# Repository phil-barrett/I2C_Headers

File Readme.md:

Welcome to I2C_Headers.  This repository is for HW designs that use the I2C header interface present on Brookwood Designs grblHAL Breakout Boards.

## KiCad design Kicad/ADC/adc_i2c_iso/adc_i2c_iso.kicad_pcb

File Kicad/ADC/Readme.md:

A simple Isolated I2C ADC interface.

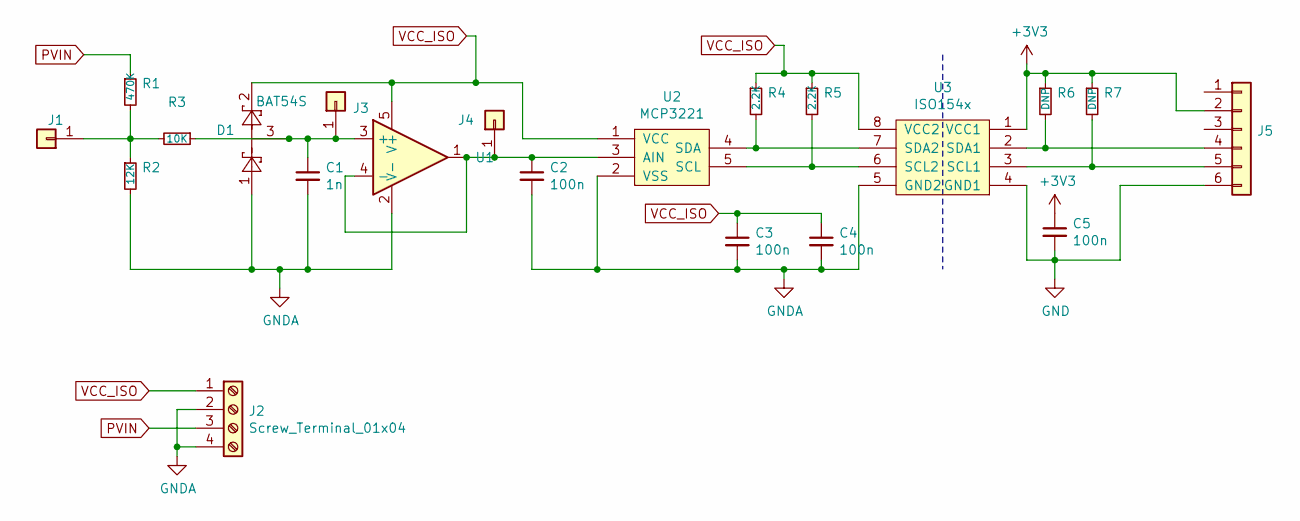
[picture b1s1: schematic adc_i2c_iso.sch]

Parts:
C1: 1n; C_0805
C2, C3, C4, C5: 100n; C_0805
D1: BAT54S; SOT-23
J1, J3, J4: Conn_01x01; Pin_Header_Straight_1x01_Pitch2.00mm
J2: Screw_Terminal_01x04; plug_term_p4
J5: Conn_01x06; Pin_Header_Straight_1x06_Pitch2.54mm
R1: 470K; R_1206
R2: 12K; R_1206
R3: 10K; R_0805; LCSC C17414
R4, R5: 2.2K; R_0805; LCSC C17520
R6, R7: DNP; R_0805; LCSC C17520
U1: MCP601-xOT; SOT-23-5; LCSC C128440
U2: MCP3221; SOT-23-5; LCSC C36310
U3: ISO154x; SOIC-8_3.9x4.9mm_P1.27mm; LCSC C179739

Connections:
+3V3: C5.1, J5.2, R6.1, R7.1, U3.1 (VCC1)
GND: C5.2, J5.6, U3.4 (GND1)
GNDA: C1.2, C2.2, C3.2, C4.2, D1.1, J2.2, J2.4, R2.2, U1.2 (V-), U2.2 (VSS), U3.5 (GND2)
unnamed: C1.1, D1.3, J3.1, R3.1, U1.3 (+)
unnamed: C2.1, J4.1, U1.1, U1.4 (-), U2.3 (AIN)
unnamed: J1.1, R1.2, R2.1, R3.2
unnamed: J5.4, R6.2, U3.2 (SDA1)
unnamed: J5.5, R7.2, U3.3 (SCL1)
unnamed: R4.2, U2.4 (SDA), U3.7 (SDA2)
unnamed: R5.2, U2.5 (SCL), U3.6 (SCL2)
PVIN: J2.3, R1.1
VCC_ISO: C3.1, C4.1, D1.2, J2.1, R4.1, R5.1, U1.5 (V+), U2.1 (VCC), U3.8 (VCC2)

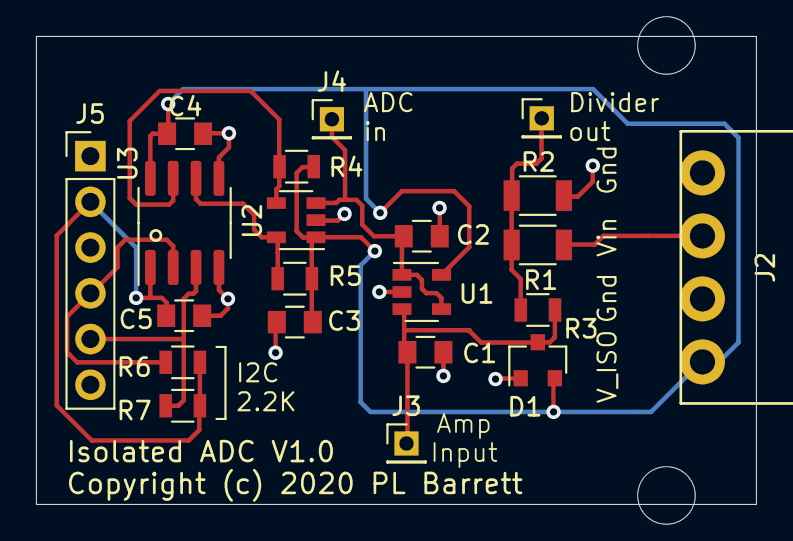
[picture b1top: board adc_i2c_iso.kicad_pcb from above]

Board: 2 copper layers, 40.0 x 26.0 mm, 21 parts (0 on the bottom side), 12 nets.

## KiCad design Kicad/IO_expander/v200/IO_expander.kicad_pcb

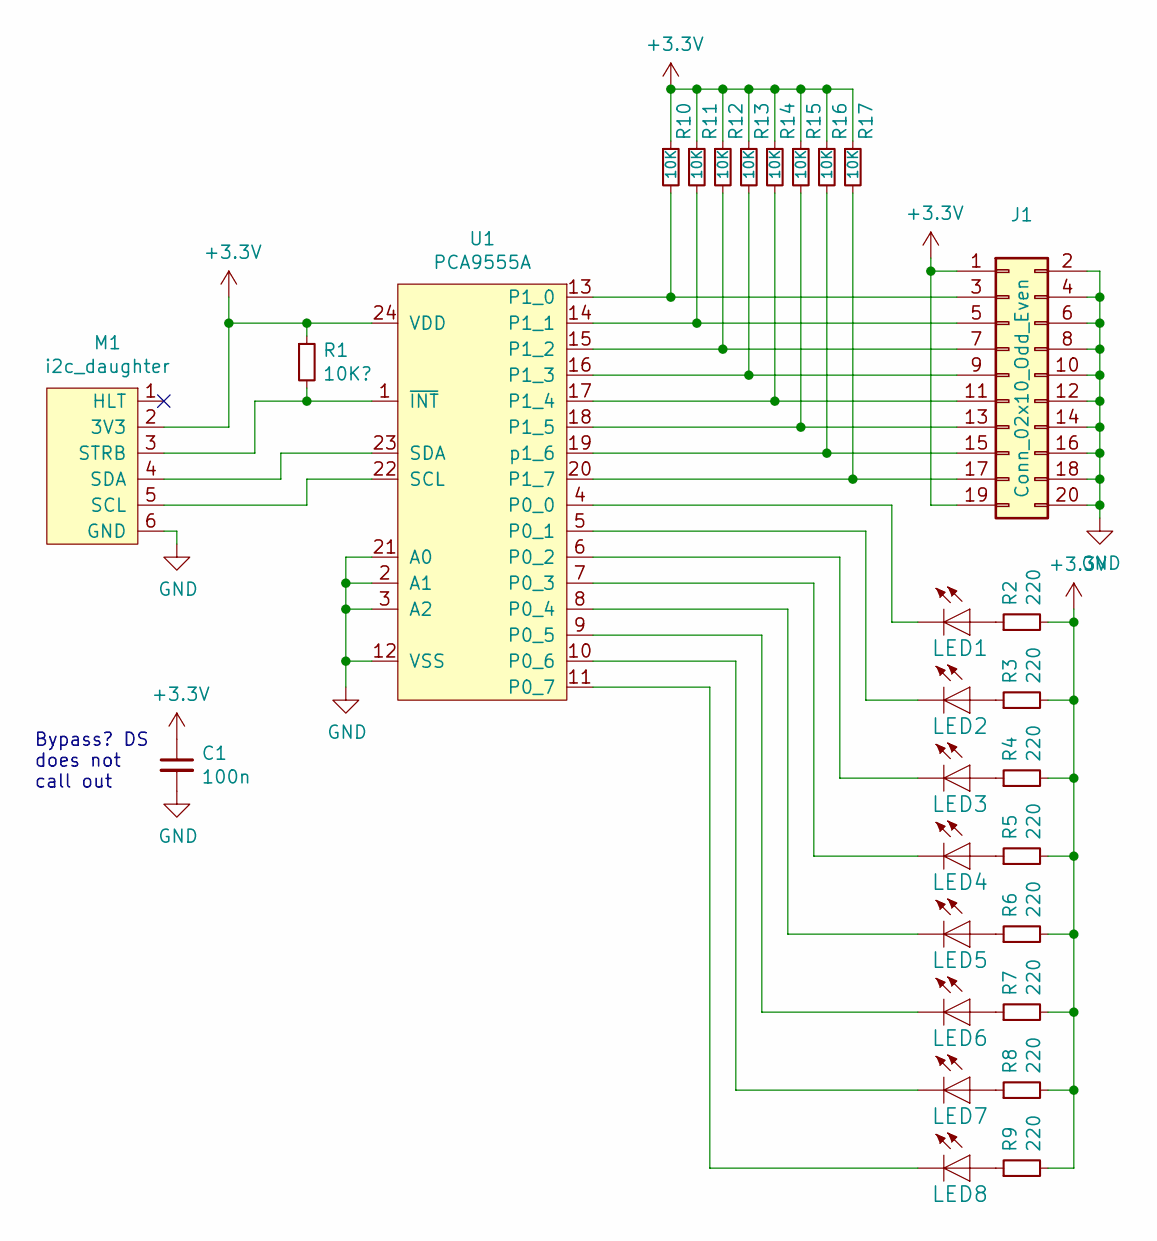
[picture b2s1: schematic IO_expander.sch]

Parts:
C1: 100n; C_0603
J1: Conn_02x10_Odd_Even; Pin_Header_Straight_2x10_Pitch2.54mm
LED1, LED2, LED3, LED4, LED5, LED6, LED7, LED8: Green_0603_19-217-GHC-YR1S2-3T; LED_0603; LCSC C72043
M1: i2c_daughter; I2C_Header
R1: 10K?; R_0603
R2, R3, R4, R5, R6, R7, R8, R9: 220; R_0603
R10, R11, R12, R13, R14, R15, R16, R17: 10K; R_0603
U1: PCA9555A; TSSOP-24_4.4x7.8mm_Pitch0.65mm

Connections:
+3V3: C1.1, J1.1, J1.19, M1.2 (3V3), R1.1, R2.2, R3.2, R4.2, R5.2, R6.2, R7.2, R8.2, R9.2, R10.1, R11.1, R12.1, R13.1, R14.1, R15.1, R16.1, R17.1, U1.24 (VDD)
GND: C1.2, J1.2, J1.4, J1.6, J1.8, J1.10, J1.12, J1.14, J1.16, J1.18, J1.20, M1.6 (GND), U1.2 (A1), U1.3 (A2), U1.12 (VSS), U1.21 (A0)
unnamed: J1.3, R10.2, U1.13 (P1_0)
unnamed: J1.5, R11.2, U1.14 (P1_1)
unnamed: J1.7, R12.2, U1.15 (P1_2)
unnamed: J1.9, R13.2, U1.16 (P1_3)
unnamed: J1.11, R14.2, U1.17 (P1_4)
unnamed: J1.13, R15.2, U1.18 (P1_5)
unnamed: J1.15, R16.2, U1.19 (p1_6)
unnamed: J1.17, R17.2, U1.20 (P1_7)
unnamed: LED1.1 (C), U1.4 (P0_0)
unnamed: LED1.2 (A), R2.1
unnamed: LED2.1 (C), U1.5 (P0_1)
unnamed: LED2.2 (A), R3.1
unnamed: LED3.1 (C), U1.6 (P0_2)
unnamed: LED3.2 (A), R4.1
unnamed: LED4.1 (C), U1.7 (P0_3)
unnamed: LED4.2 (A), R5.1
unnamed: LED5.1 (C), U1.8 (P0_4)
unnamed: LED5.2 (A), R6.1
unnamed: LED6.1 (C), U1.9 (P0_5)
unnamed: LED6.2 (A), R7.1
unnamed: LED7.1 (C), U1.10 (P0_6)
unnamed: LED7.2 (A), R8.1
unnamed: LED8.1 (C), U1.11 (P0_7)
unnamed: LED8.2 (A), R9.1
unnamed: M1.3 (STRB), R1.2, U1.1 (~INT)
unnamed: M1.4 (SDA), U1.23 (SDA)
unnamed: M1.5 (SCL), U1.22 (SCL)

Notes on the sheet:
Bypass? DS does not call out

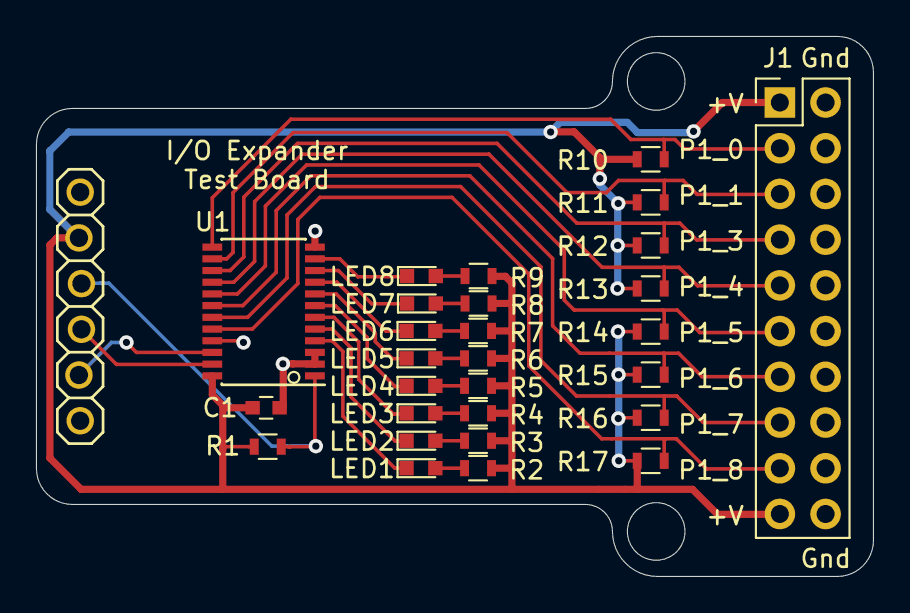
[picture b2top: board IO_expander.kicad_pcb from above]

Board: 2 copper layers, 46.5 x 30.0 mm, 29 parts (0 on the bottom side), 29 nets.

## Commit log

2021-06-06 Add files via upload
    V2.0 of I/O Expander Test Board

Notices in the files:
Kicad/ADC/adc_i2c_iso/adc_i2c_iso.kicad_pcb:
Copyright (c) 2020 PL Barrett
